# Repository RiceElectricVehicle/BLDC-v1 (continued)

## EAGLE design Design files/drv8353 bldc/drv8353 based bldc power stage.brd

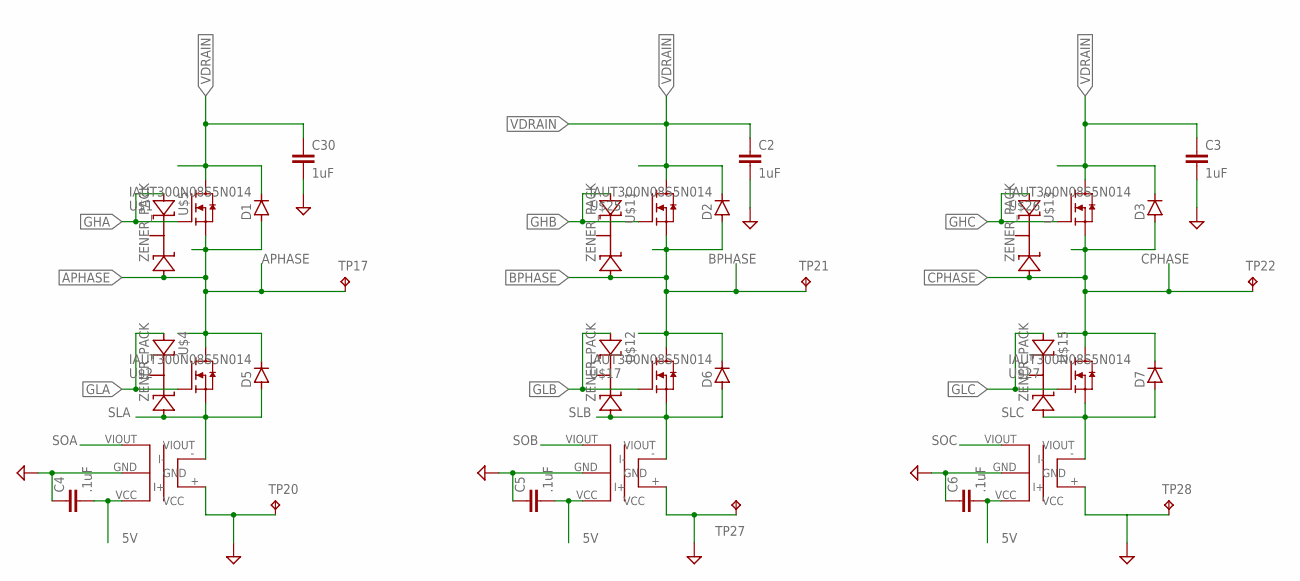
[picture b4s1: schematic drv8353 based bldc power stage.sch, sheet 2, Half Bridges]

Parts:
C2, C3, C30: 1uF; C1206
C4, C5, C6: .1uF; C0603K
D1, D2, D3, D5, D6, D7: D-SOD123; SOD123
TP17, TP20, TP21, TP22, TP27, TP28: TPB1,27; B1,27
U$1, U$2, U$17, U$25, U$26, U$27: IAUT300N08S5N014; PG-HSOF-8-1_MODIFIED
U$3, U$9, U$10: ACS770LCB-050B-PFF-T; LEADFORM_PFF
U$4, U$5, U$11, U$12, U$13, U$15: ZENER_PACK; SOT23

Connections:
5V: C4.2, C5.2, C6.2, U$3.VCC, U$9.VCC, U$10.VCC; also elsewhere on the board
APHASE: D1.2 (A), D5.LINE (C), TP17.TP, U$1.2 (S), U$1.3 (S), U$1.4 (S), U$1.5 (S), U$1.6 (S), U$1.7 (S), U$1.8 (S), U$1.10 (S), U$1.11 (S), U$1.12 (S), U$1.13 (S), U$1.14 (S), U$1.15 (S), U$2.9 (D), U$2.16 (D), U$2.17 (D), U$2.18 (D), U$2.19 (D), U$5.1 (END1); also elsewhere on the board
BPHASE: D2.2 (A), D6.LINE (C), TP21.TP, U$11.1 (END1), U$17.9 (D), U$17.16 (D), U$17.17 (D), U$17.18 (D), U$17.19 (D), U$25.2 (S), U$25.3 (S), U$25.4 (S), U$25.5 (S), U$25.6 (S), U$25.7 (S), U$25.8 (S), U$25.10 (S), U$25.11 (S), U$25.12 (S), U$25.13 (S), U$25.14 (S), U$25.15 (S); also elsewhere on the board
CPHASE: D3.2 (A), D7.LINE (C), TP22.TP, U$13.1 (END1), U$26.2 (S), U$26.3 (S), U$26.4 (S), U$26.5 (S), U$26.6 (S), U$26.7 (S), U$26.8 (S), U$26.10 (S), U$26.11 (S), U$26.12 (S), U$26.13 (S), U$26.14 (S), U$26.15 (S), U$27.9 (D), U$27.16 (D), U$27.17 (D), U$27.18 (D), U$27.19 (D); also elsewhere on the board
GHA: U$1.1 (G), U$5.2 (END2); also elsewhere on the board
GHB: U$11.2 (END2), U$25.1 (G); also elsewhere on the board
GHC: U$13.2 (END2), U$26.1 (G); also elsewhere on the board
GLA: U$2.1 (G), U$4.2 (END2); also elsewhere on the board
GLB: U$12.2 (END2), U$17.1 (G); also elsewhere on the board
GLC: U$15.2 (END2), U$27.1 (G); also elsewhere on the board
GND: C2.2, C3.2, C4.1, C5.1, C6.1, C30.2, TP20.TP, TP27.TP, TP28.TP, U$3.+ (I+), U$3.GND, U$9.+ (I+), U$9.GND, U$10.+ (I+), U$10.GND; also elsewhere on the board
SLA: D5.2 (A), U$2.2 (S), U$2.3 (S), U$2.4 (S), U$2.5 (S), U$2.6 (S), U$2.7 (S), U$2.8 (S), U$2.10 (S), U$2.11 (S), U$2.12 (S), U$2.13 (S), U$2.14 (S), U$2.15 (S), U$3.- (I-), U$4.1 (END1); also elsewhere on the board
SLB: D6.2 (A), U$9.- (I-), U$12.1 (END1), U$17.2 (S), U$17.3 (S), U$17.4 (S), U$17.5 (S), U$17.6 (S), U$17.7 (S), U$17.8 (S), U$17.10 (S), U$17.11 (S), U$17.12 (S), U$17.13 (S), U$17.14 (S), U$17.15 (S); also elsewhere on the board
SLC: D7.2 (A), U$10.- (I-), U$15.1 (END1), U$27.2 (S), U$27.3 (S), U$27.4 (S), U$27.5 (S), U$27.6 (S), U$27.7 (S), U$27.8 (S), U$27.10 (S), U$27.11 (S), U$27.12 (S), U$27.13 (S), U$27.14 (S), U$27.15 (S); also elsewhere on the board
SOA: U$3.VIOUT; also elsewhere on the board
SOB: U$9.VIOUT; also elsewhere on the board
SOC: U$10.VIOUT; also elsewhere on the board
VDRAIN: C2.1, C3.1, C30.1, D1.LINE (C), D2.LINE (C), D3.LINE (C), U$1.9 (D), U$1.16 (D), U$1.17 (D), U$1.18 (D), U$1.19 (D), U$25.9 (D), U$25.16 (D), U$25.17 (D), U$25.18 (D), U$25.19 (D), U$26.9 (D), U$26.16 (D), U$26.17 (D), U$26.18 (D), U$26.19 (D); also elsewhere on the board

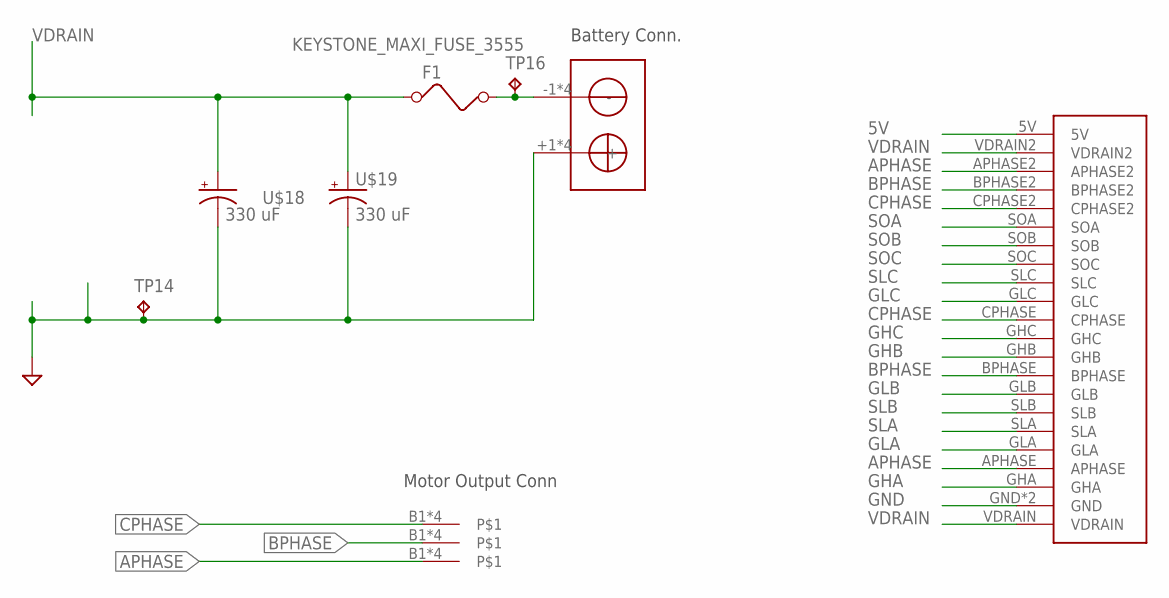
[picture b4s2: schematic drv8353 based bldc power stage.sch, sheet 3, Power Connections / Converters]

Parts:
F1: KEYSTONE_MAXI_FUSE_3555; KEYSTONE_MAXI_FUSE_CLIP_3555
TP14, TP16: TPB1,27; B1,27
U$6, U$7, U$8: MINI-PP75
U$14: POWER_STAGE_CONNECTOR; POWER_STAGE_CONNECTION
U$16: SB50; MINI-SB-50
U$18, U$19: 330 uF; SM_RADIAL_K16_1PRIMARY

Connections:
5V: U$14.5V; also elsewhere on the board
APHASE: U$8.B1, U$8.B2, U$8.B3, U$8.B4, U$14.APHASE, U$14.APHASE2; also elsewhere on the board
BPHASE: U$7.B1, U$7.B2, U$7.B3, U$7.B4, U$14.BPHASE, U$14.BPHASE2; also elsewhere on the board
CPHASE: U$6.B1, U$6.B2, U$6.B3, U$6.B4, U$14.CPHASE, U$14.CPHASE2; also elsewhere on the board
GHA: U$14.GHA; also elsewhere on the board
GHB: U$14.GHB; also elsewhere on the board
GHC: U$14.GHC; also elsewhere on the board
GLA: U$14.GLA; also elsewhere on the board
GLB: U$14.GLB; also elsewhere on the board
GLC: U$14.GLC; also elsewhere on the board
GND: TP14.TP, U$14.GND, U$14.GND2 (GND), U$16.+1 (+), U$16.+2 (+), U$16.+3 (+), U$16.+4 (+), U$18.-, U$19.-; also elsewhere on the board
unnamed: F1.B1 (2), F1.B2 (2), TP16.TP, U$16.-1 (-), U$16.-2 (-), U$16.-3 (-), U$16.-4 (-)
SLA: U$14.SLA; also elsewhere on the board
SLB: U$14.SLB; also elsewhere on the board
SLC: U$14.SLC; also elsewhere on the board
SOA: U$14.SOA; also elsewhere on the board
SOB: U$14.SOB; also elsewhere on the board
SOC: U$14.SOC; also elsewhere on the board
VDRAIN: F1.A1 (1), F1.A2 (1), U$14.VDRAIN, U$14.VDRAIN2, U$18.+, U$19.+; also elsewhere on the board

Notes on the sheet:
Battery Conn.
Motor Output Conn

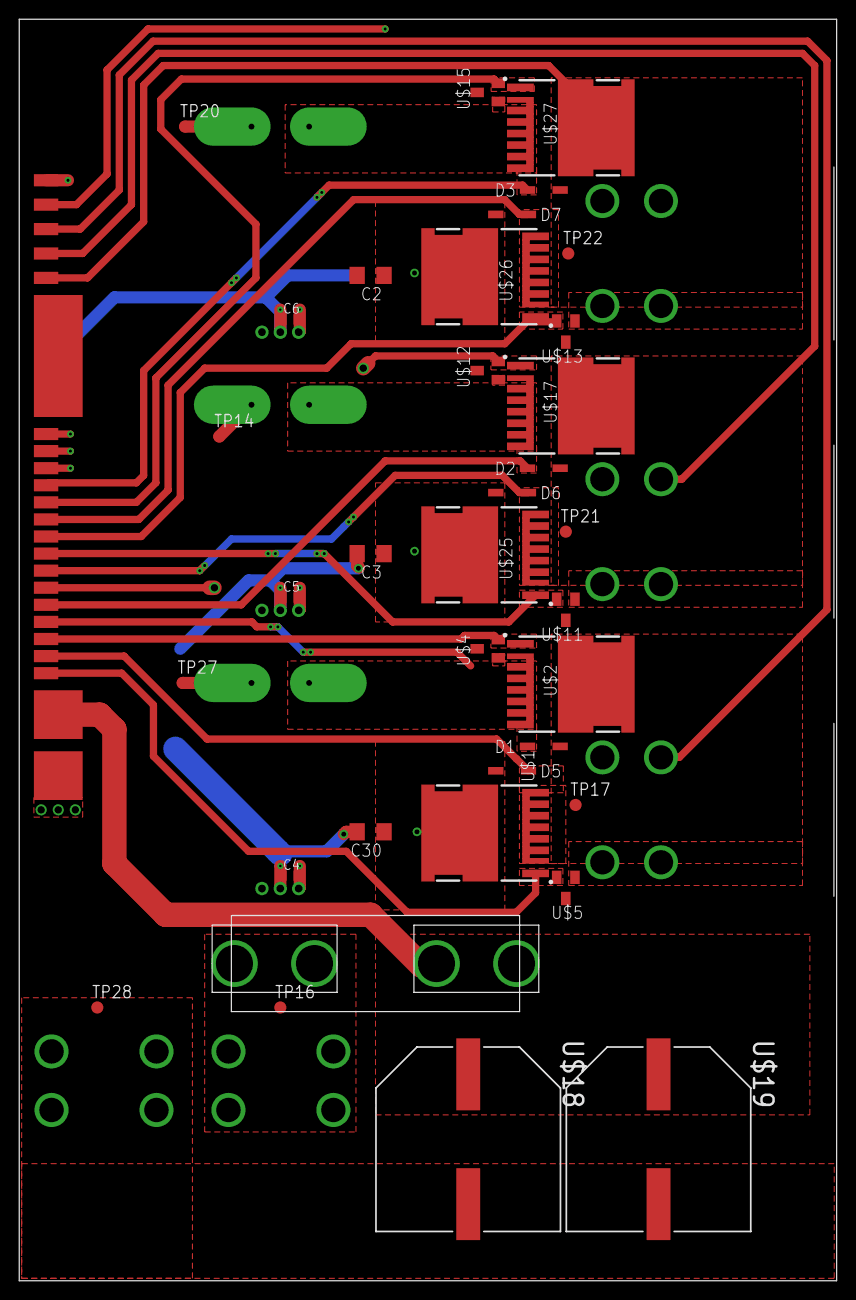
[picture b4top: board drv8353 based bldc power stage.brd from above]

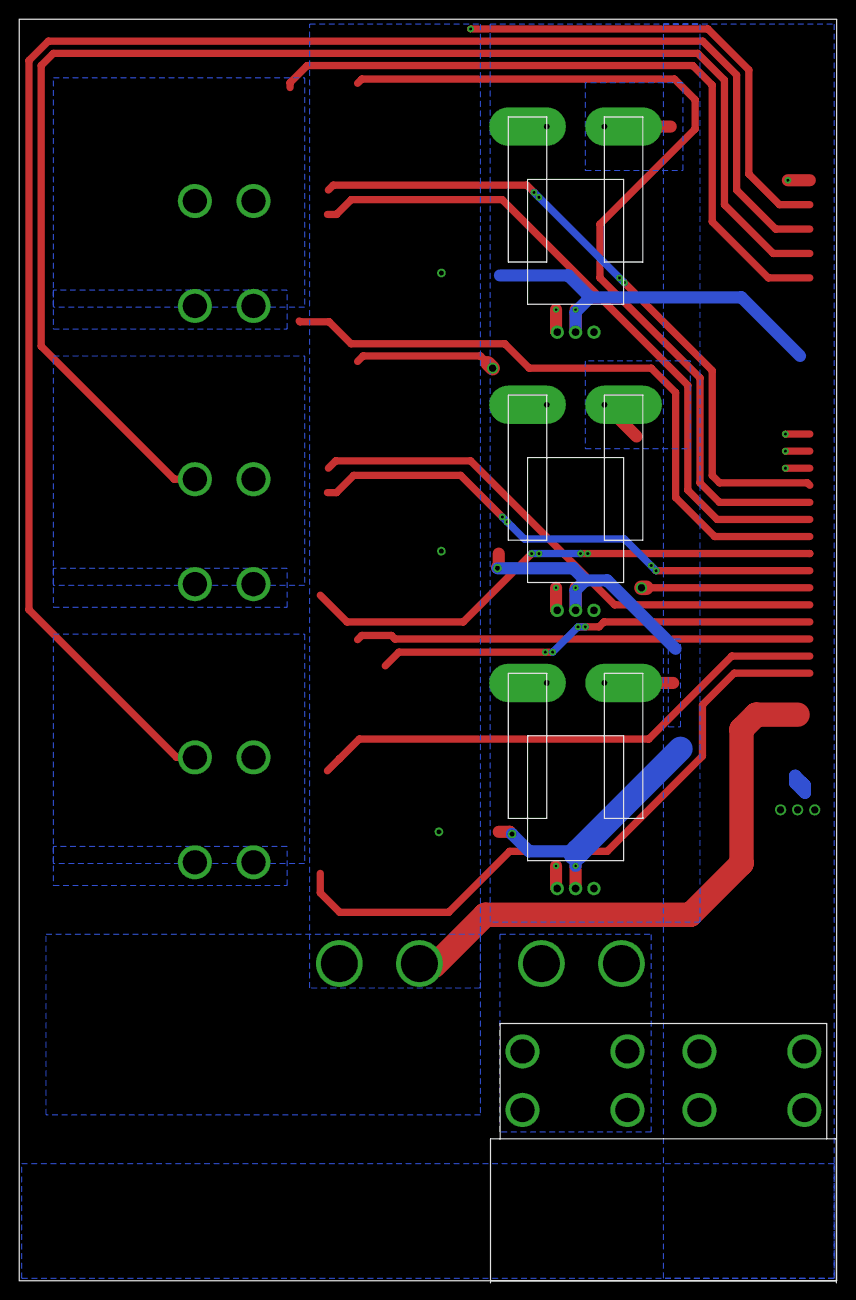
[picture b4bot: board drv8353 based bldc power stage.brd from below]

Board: 4 copper layers, 85.1 x 131.3 mm, 43 parts (4 on the bottom side), 19 nets.

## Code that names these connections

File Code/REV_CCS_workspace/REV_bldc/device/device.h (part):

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#define DEVICE_CFG_DRV_ENABLE       GPIO_12_GPIO12  // "pinConfig" for Enable

#define DRV_NFAULT_GPIO_PIN         34U
#define DEVICE_CFG_NFAULT           GPIO_34_GPIO34  // "pinConfig" for nFAULT

#define INHA                        0U
#define INLA                        1U
#define INHB                        6U
#define INLB                        7U
#define INHC                        2U
#define INLC                        3U

//
// LEDs
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
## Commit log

2019-10-13 Initial files
2019-10-19 adds GND symbols, some part names
2019-10-19 splits output stagge and logic into separate sheets
2019-10-19 adds LED and pullup on nFault, rearranges drv internal buck ouput components
2019-10-19 adds frame to both sheets
2019-10-19 fixes frames to refer to high/low side and bridge number
2019-10-20 added most component values
    added compenent values except for ones that we really do need to figure out
    also added the motor output connector
2019-10-21 adds schottky diodes in parallel with high side body diodes
2019-10-22 separates AGND and GND on DRV chip
2019-10-22 adds debug header, adds lots of test points
2019-10-24 updated boosterpack dock to match C2000 F28004C launchpad
2019-10-24 finishes updates to connectors, adds test points, renames QEP interface back to hall effect
2019-10-24 adds schematic sheet for power connectors & converters
2019-10-26 added hall sensor connector
2019-10-26 added HCM connector to library
2019-10-27 adds motor controller code to version control system
2019-10-28 replaced generic fuse with automotive style blade fuse
    fuse chosen was the maxi standard becasue the regular ATO fuses max out at 40 amps and I'm not sure if that's enough for how we want to fuse this board
2019-10-28 created communications boards, combined 2x10 headers
2019-10-28 did some wiring and added led's
2019-10-28 added pot, and headers for spi , i2c, analog pins, and the input spi signal
2019-10-28 reordered header and did a tenative layout
2019-10-28 adds power switch to motor controller
2019-10-28 adds header to select between battery and buck supply for VM
    can also be used to power VM off external supply
2019-10-28 code changes
2019-10-28 modifies power button, debug header, AGND
2019-10-29 fixed f/b annotation issue
    the components casuing the issue were the ones involved in the merge. I just deleted and then recreated the board file to fix it.
2019-10-29 moved analog signals top adc-b pins
2019-10-29 added tenative current sense resistor and modified schematic to use kelvin stly current shunt
    current shunt is still valueless, but the package suports the range of 2-3 mohm with a tolerence of either .1% or .5%. a very similar package can do 1-2 mohm if we decide that's what we want.
2019-10-29 adds ADC_C initialization in code
2019-10-29 changes board grid to 1 mm, 0.1mm grid, changes package for schottky diodes
2019-10-29 finalizes package of schottky diodes
2019-10-29 updated DRC and stackup to match OSHPark 2oz 0.8mm service
2019-10-29 updates DRC to use OSHPark 2oz 0.8mm service
2019-10-29 moves stuff around :100:
2019-10-30 removes passives values, moves location of bulk caps and battery input,
2019-10-30 font size, drv layout progress
2019-10-30 adds draft layout for drv buck regulator circuit
2019-10-30 modified silkscreen to show relevant information
2019-10-30 improves on drv buck layout
2019-10-30 partial draft layout of charge pump and FET inputs to DRV
2019-10-30 refines layout for drv charge pump external circuit and current sense on phase A
2019-10-30 modified current shunt and fets to not use thermals
2019-10-30 moved fets and signals around
2019-10-30 adds layout for Shunt amplifiers on B and C phases (minus capacitor on C)
2019-10-31 more shifting
2019-10-31 moves fets around
2019-10-31 routed all gate and current sense signals
2019-10-31 turned thermals off for output connector, added via stiching and planes across all layers
2019-10-31 turned off thermals for output connector, added vias and planes on all layers
2019-10-31 Revert "turned thermals off for output connector, added via stiching and planes across all layers"
    This reverts commit 143dc5638347258ee57d4fd3331359361aa11012.
2019-10-31 rerouted current sense signals to layer 15
2019-10-31 modifies current sense traces for noise immunity
2019-11-01 small fix for spi mosi route
2019-11-01 adds GND planes, vias
2019-11-01 separates motor controller ground planes from drv ground plane
2019-11-01 fixes some small issues with plane fills
2019-11-01 rerouted Vdrain and added vias to improve FET ground path, also reoriented launchpad dock for better signal routing
2019-11-03 routed isense signals
2019-11-03 routed digital signals
2019-11-03 spaced digital signals to reduce coupling
2019-11-03 all components except test points and agnd stuff placed and routed
2019-11-03 placed and routed some parts I missed
2019-11-03 reroutes AGND and PGND
2019-11-04 small revisions to layout
2019-11-04 via stitched the board
2019-11-04 placed most test points
2019-11-04 edits stackup
2019-11-09 fixes: c31-33 closer to fets, spacing of ABCPhases, layout of drv internal buck regulator
2019-11-09 some small changes
2019-11-14 remoeved extraneous test points
2019-11-14 moved CPHASE current sense capacitor to be consistent with other phases
2019-11-14 added little bits of routing to resolve all air wires
2019-11-15 slight change to 3v3 ldo
2019-11-16 added low side flybacks
    added low side flybacks
2019-11-18 adds zener and bypas header for LDO
2019-11-18 silkscreen pass, slightly moved fuse to prevent part collision
2019-11-20 corrected drc
2019-11-20 fixed board for jlpcb 2oz service
2019-11-22 moves VSENA away from ADC B; got rid of some vias by the text
2019-11-22 adds interrupt routines for ADC A,B,C
2019-11-25 adds 3d packages for some parts
2019-11-25 added more 3d packages
2019-12-29 switched to hall effect current sense and drv8350RS
2019-12-29 started layout of power stage
2019-12-30 large components tenetively placed
2019-12-31 created tenetive board connection part, did some initial routing
2019-12-31 finished most of power stage routing
2020-01-17 fixed debug header
2020-01-17 more routing
2020-01-18 beefed up some planes
2020-01-18 reworked driver stage to work with board interface
2020-02-01 adds enable link to comm board
2020-02-26 adds chip select to com board
2020-02-27 reroute to match aux
2020-04-06 replaces fets with ones we can actually get (are also 100v capable instead of 80)
2020-04-06 adds correct circuitry for hall effect sensors
2020-04-06 adds gate zeners protection
2020-04-06 expanded debug header
2020-04-06 adjusts component spacing
2020-04-06 moves 3v3 rail closer to drv
2020-04-06 small trace placement tweaks
2020-04-06 adds space for larger fets
2020-04-07 lays out c2000 dock
2020-04-07 extends ground pour
2020-04-07 adds resistor between enable and c2000
2020-04-07 widens main power return path
2020-04-07 routed fet traces to drv
